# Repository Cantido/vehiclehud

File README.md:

VehicleHUD [![Build Status][ci-img]][ci-link]
=============================================

The purpose of this project is to design and build a projected heads-up
display for a car that is projected on to the windshield. This system will
pull vehicle information from the OBD-II diagnostic jack located in all modern
cars.

Compiling Vehiclehud
--------------------

The main program can be built simply using Make:

```shell
cd src && make
```

Using Vehiclehud
------------------
There is no configuration necessary. Just execute the program that is created
by ```make```. Vehiclehud will attempt to connect to an OBD-II adapter at a
file location defined in the source. If it can connect, it will begin polling
the OBD device for vehicle information and printing the current RPM to
standard output.

OBD-II Adapter Support
----------------------
Currently this software only supports the ELM327 OBD-II adapter. It is a goal
of this project to encapsulate adapter functions so that adding support for
other adapters is possible.

* * * * * * * * * * * * * * * * * * * * * * * * * * * * * * * * * * * * * * * *

Copyright 2013 Robert Richter and Aaron Hall  
Distributed under the terms of the GNU GPL.

[ci-img]: https://travis-ci.org/Cantido/vehiclehud.png?branch=master
[ci-link]: https://travis-ci.org/Cantido/vehiclehud

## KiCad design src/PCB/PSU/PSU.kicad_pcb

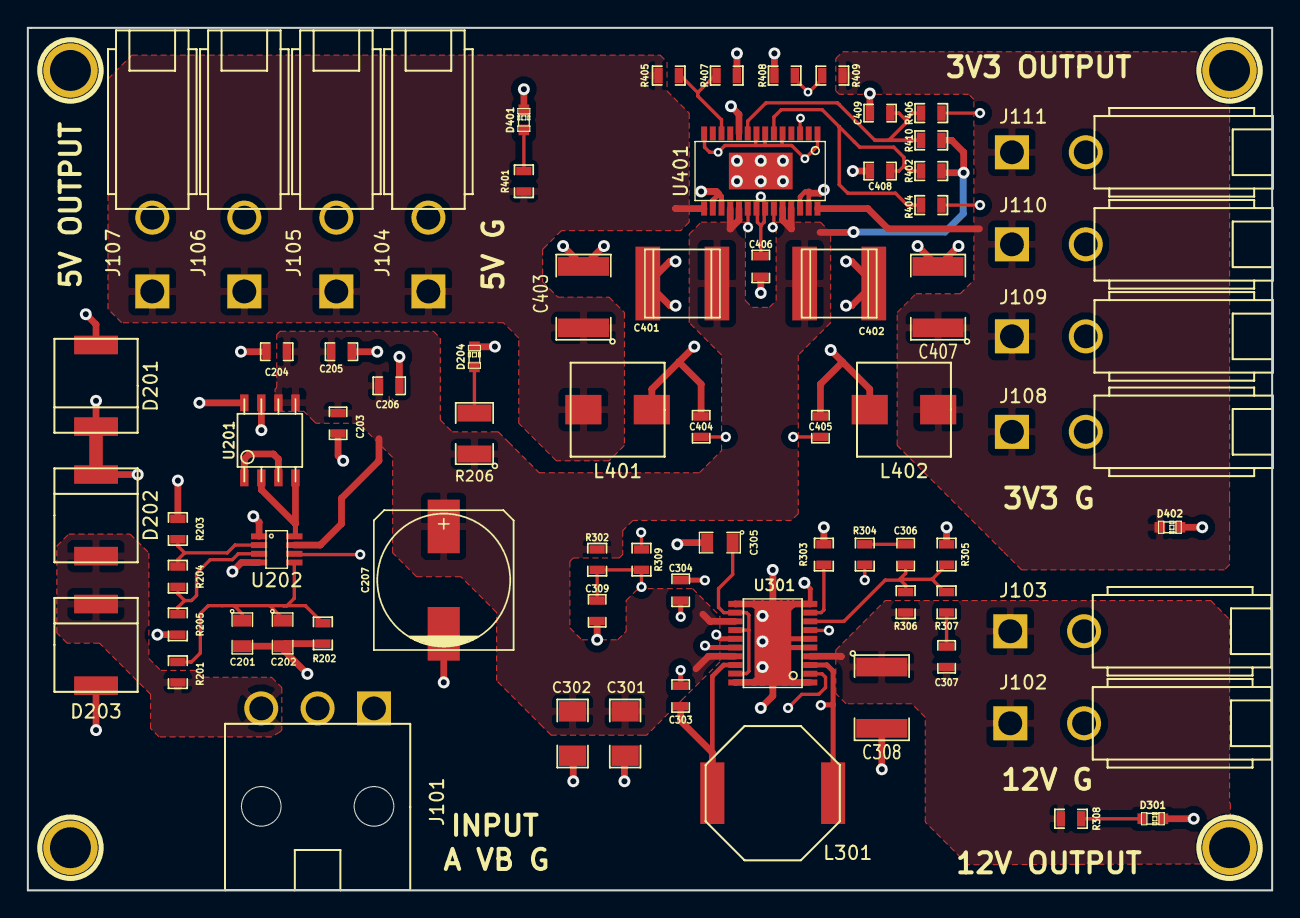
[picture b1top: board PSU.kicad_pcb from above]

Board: 4 copper layers, 92.7 x 64.3 mm, 77 parts (0 on the bottom side), 36 nets.

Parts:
1PIN, 1PIN#2, 1PIN#3, 1PIN#4: P***; 1pin
C201: 0.1uF; SM0805
C202: 0.01uF; SM0805
C203, C204: 0.01u; SM0603_Capa
C205, C206: 0.1u; SM0603_Capa
C207: 100uF; c_elec_10x10
C301, C302: 10uF; SM1206
C303, C304, C309, C404, C405, C408, C409: 0.1uF; SM0603_Capa
C305: 4.7uF; SM0805
C306: 820pF; SM0603_Capa
C307: 33pF; SM0603_Capa
C308, C403, C407: 22uF; SM1812
C401, C402: 47uF; c_2220
C406: 2.2uF; SM0603_Capa
D201, D203: SMCJ40A; DO-214AB(SMC)
D202: SCHOTTKY; DO-214AB(SMC)
D204, D301, D401, D402: BLUE_LED; LED-0603
J101: VIN; mini-fit-jr-3
J102: 12V_1; mini-fit-jr-2
J103: 12V_2; mini-fit-jr-2
J104: 5V_1; mini-fit-jr-2
J105: 5V_2; mini-fit-jr-2
J106: 5V_3; mini-fit-jr-2
J107: 5V_4; mini-fit-jr-2
J108: 3_3V_1; mini-fit-jr-2
J109: 3_3V_2; mini-fit-jr-2
J110: 3_3V_3; mini-fit-jr-2
J111: 3_3V_4; mini-fit-jr-2
L301: 10uH; L10
L401: 1.5uH; L6.9
L402: 1uH; L6.9
R201, R302, R402, R410: 100k; SM0603_Resistor
R202, R307, R407, R408: 10k; SM0603_Resistor
R203: 1.82M; SM0603_Resistor
R204: 243k; SM0603_Resistor
R205: 59k; SM0603_Resistor
R206: 560; SM1210
R303: 35.7k; SM0603_Resistor
R304: 40.2k; SM0603_Resistor
R305: 90.9k; SM0603_Resistor
R306: 1M; SM0603_Resistor
R308: 430; SM0603_Resistor
R309, R404, R406: 0; SM0603_Resistor
R401: 91; SM0603_Resistor
R405: 73.2k; SM0603_Resistor
R409: 45.3k; SM0603_Resistor
U201: SI4946; so-8
U202: LTC4365; tsot-23
U301: LTC3115-1; tssop-20-epad
U401: LTC3633A-1; tssop-28-epad

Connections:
/5V and 3.3V Supply/3_3V: C407.1, D402.1, J108.1, J109.1, J110.1, J111.1, L402.2, R409.2, U401.28
/5V and 3.3V Supply/5V: C403.1, J104.1, J105.1, J106.1, J107.1, L401.1, R401.1, R405.1, U401.15
/12V Supply/12V: C307.1, C308.1, J102.1, J103.1, R306.1, R308.1, U301.4
/12V Supply/RUN: R309.1, R404.1, R406.1, U202.6
/PSU Protection/ACC: D202.1, D203.2, J101.3, R201.1
/PSU Protection/VBATT: D201.2, D202.2, J101.2, R203.1, U201.7, U201.8, U202.1
GND: C201.2, C202.2, C203.2, C204.2, C205.2, C206.2, C207.2, C301.2, C302.2, C305.2, C308.2, C309.2, C401.2, C402.2, C403.2, C406.2, C407.2, C408.2, C409.2, D201.1, D203.1, D204.2, D301.2, D401.2, D402.2, J101.1, J102.2, J103.2, J104.2, J105.2, J106.2, J107.2, J108.2, J109.2, J110.2, J111.2, R202.2, R205.2, R303.2, R305.2, R407.2, R408.2, U202.4, U301.1, U301.5, U301.6, U301.10, U301.11, U301.20, U301.21, U401.10, U401.29
unnamed: C201.1, C202.1, R201.2, R202.1, U202.5
unnamed: D204.1, R206.2
unnamed: R203.2, R204.1, U202.2
unnamed: R204.2, R205.1, U202.3
unnamed: U201.2, U201.4, U202.8
unnamed: U201.1, U201.3
unnamed: C305.1, U301.12, U301.14, U301.19
unnamed: C307.2, R307.1
unnamed: C304.2, U301.15
unnamed: D301.1, R308.2
unnamed: C306.2, R305.1, R306.2, R307.2, U301.8
unnamed: R304.2, U301.7
unnamed: C306.1, R304.1
unnamed: R303.1, U301.9
unnamed: C309.1, R302.2, R309.2, U301.2
unnamed: C303.1, L301.1, U301.18
unnamed: C303.2, U301.16
unnamed: C304.1, L301.2, U301.3
unnamed: C405.1, U401.23
unnamed: C404.1, U401.20
unnamed: C404.2, L401.2, U401.16, U401.17
unnamed: C406.1, U401.1, U401.5, U401.7, U401.8, U401.14, U401.21, U401.22
unnamed: C408.1, R402.2, R404.2, U401.6
unnamed: C409.1, R406.2, R410.2, U401.9
unnamed: D401.1, R401.2
unnamed: C405.2, L402.1, U401.26, U401.27
unnamed: R408.1, R409.1, U401.3
unnamed: R405.2, R407.1, U401.12
VCC: C203.1, C204.1, C205.1, C206.1, C207.1, C301.1, C302.1, C401.1, C402.1, R206.1, R302.1, R402.1, R410.1, U201.5, U201.6, U202.7, U301.13, U301.17, U401.18, U401.19, U401.24, U401.25

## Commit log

2013-05-02 Wrote inital description
2013-05-02 Fixed Markdown formatting
2013-05-02 Minor adjustment to language
2013-05-02 Applied GPL
2013-05-02 Fixed ordered list formatting
2013-05-02 Added a target to clean the folder of .exe files
2013-05-02 Added newline to the end
2013-05-02 Turning on all compiler warnings
2013-05-02 Add serial configuration and initialization code
2013-05-02 Add GNU GPL statement
2013-05-02 Make error messages display target file location
2013-05-02 Extract command variables
2013-05-02 Add stackdump files to clean target
2013-05-02 Improve error handling and feedback
2013-05-02 Add newline to end of file
2013-05-02 Extracted serial connection operations to a function
2013-05-02 Map NL to CR-NL on output
2013-05-02 Disable output translation of newlines. We'll handle this ourselves
2013-05-02 Remove oflag settings, currently uneeded
2013-05-02 Make reads blocking
2013-05-02 Re-enable nonblocking IO for testing purposes
2013-05-02 Add testing feedback to verify communication with ELM chip
2013-05-02 Learn to count
2013-05-02 Fully describe our requirements from the OBD
2013-05-02 Add a missing period
2013-05-02 Replace horizontal rules with proper headers, for GitHub
2013-05-02 Fix printing of carriage return character
2013-05-03 Extract chip read test to a function
2013-05-03 Add forward declaration and variable declaration
2013-05-03 Rename test_reset to obd_init
2013-05-03 Add documentation for functions
2013-05-04 Add function get_data to get data from OBD
2013-05-06 Write carriage return after request to terminate string
2013-05-06 Fix sending of carriage return at end of request string
2013-05-06 Use strtol instead of atoi to correctly parse hex string
2013-05-06 Remove unecessary parameter to get_data
2013-05-06 Remove unused local variables
2013-05-06 Extract line end character to DEFINE directive
2013-05-06 Add some debug printing
2013-05-07 Remove unnecessary variable
2013-05-07 Add forward declaration for get_data
2013-05-07 Create debug loop to print RPM every 2 seconds
    If we make it that far...
2013-05-08 Fix spelling error in previous commit
    Note to self: compile before commit
2013-05-08 Extract OBD PID defintions into its own header
2013-05-08 Add OBD header file to repo
2013-05-08 Extract OBD PID defintions into its own header
    Add OBD header file to repo
2013-05-08 Add z modifier to ssize_t format strings
2013-05-09 Extract get of RPM into a function
2013-05-09 Turn on compiler warnings the correct way
2013-05-09 Extracted OBD data functions to obd.c
2013-05-14 Add .gch files to clean target
2013-05-14 Extracted ELM327-specific functions to elm327.c
    Functions requred by obd.c are now preprocessor defines in obd.c pointing to
    elm327's particular get_elm327_data function
2013-05-14 Add first set of PID definitions
2013-06-17 Create gh-pages branch via GitHub
2013-06-19 Configure for the Raspberry Pi USB port
2013-06-25 Added sample C# project for OBD communication.
2013-08-02 Convert to C++ Project
2013-08-02 Add make target to .travis.yml
2013-08-02 Add Travis-CI build status image
2013-08-02 Convert back to C project
2013-08-02 Convert to C project
2013-08-02 Minor cleanup of compiler and debug warnings
2013-08-13 Remove implementation info from readme, add usage info
2013-08-13 Clarify README language
2013-08-14 Initial add of Image to Byte Array project.
    This C# program will convert a monochrome bitmap to a byte array. The
    byte array is in the correct format for the Noritake 128x64 VFD.
2013-08-14 Initial commit of hardware and firmware.
    Adding initial PCB designs and AVR testing.
2013-08-15 Modify to use GNU Autotools
2013-08-15 Add autogen script to build process
2013-08-15 Make travis build generate Autotools files
2013-08-15 Remove Autoconf version requirement
2013-08-15 Disable Travis's execution of tests, since we have none
2013-08-15 Remove redundancy from Travis build script
2013-08-16 Reorganized
2013-08-16 Modified to use GNU Autotools
2013-08-23 Added main firmware project and the main board PCB project.
2013-08-23 Move all source files into src directory
2013-08-23 Move all datasheets into doc directory
2013-08-23 Remove binary folders
2013-09-03 Updated PCB projects.
2013-09-05 Simplify terminal settings
2013-09-05 Python makes everything better
2013-09-06 Make main print debug info for now
2013-09-06 Update README to reflect migration to Python
2013-09-10 More changes to the main board schematic.
2013-09-17 Refactor device commands and improve IO speed
2013-09-17 Create integrationtests.py containing tests for an installed system
2013-09-17 Move connect functionality out of init and into its own method
2013-09-17 Check your code for syntax before you commit it
2013-09-17 Fix data requests
2013-09-17 Create simple test for data requests
2013-09-18 Move PDFs out of repo and into the Dropbox
2013-09-19 Fix data requests and add several data methods
2013-09-19 Create more tests
2013-09-19 Create prototype display modes
2013-09-19 Add exception handling, and add string members to data functions
2013-09-19 Add more error handling to data requests
2013-09-19 Change MockSerial to MockDevice
    MockDevice inherits from ELM327 and overrides serial and IO methods
    to allow us to test the rest of the class.
2013-09-19 Remove merge stuff
2013-09-19 Add IDLE folder to be ignored
2013-09-19 Properly use string formatting for exception message
2013-09-19 Extract method for splitting a request into mode, pid, and payload
2013-09-19 Allow users to set expected mock response
2013-10-10 Created final report
2013-10-10 Fix typo
2013-10-10 Add LaTeX-specific files to .gitignore
2013-10-10 Refactor data request function
    There's a lot of nasty static methods in here now, though. :c
2013-10-10 Put executive summary in present and past tense
2013-10-10 Update project team section for present tense
2013-10-10 Update Aaron's email address
2013-10-10 Move each section to its own file
2013-10-10 Create files for each section
2013-10-10 Create introduction
2013-10-14 Add references
2013-10-14 Move image to display after section starts
2013-10-14 Draft project objectives
2013-10-14 Add more LaTeX types to gitignore
    From https://github.com/github/gitignore/blob/master/LaTeX.gitignore
2013-10-14 Add more Python types to gitignore
    From https://github.com/github/gitignore/blob/master/Python.gitignore
2013-10-19 added OBD code implemented in C
2013-10-22 Fix compile errors and add debug print statements
2013-10-22 Refactor: extract baud and read method
    Also modified formatting of entire file since I tore it up while working
2013-10-22 Refactor: extract initialization segment
2013-10-22 Remove unused buffer
2013-10-22 Remove an unnecessary sleep while reading
2013-10-22 Extract method to get RPM
2013-10-22 Remove unused variables
2013-10-22 Refactor: extract more methods
2013-10-22 Refactor: make formatting consistent
    Used GNU Indent with the -linux option
2013-10-23 Fix "ON" detection
2013-10-23 Add Makefile for C code
2013-10-23 Set Travis to build C code
2013-10-24 updated obd code
2013-10-24 Fix compile errors
2013-10-24 Change formatting
2013-10-24 Add formatting target to makefile
2013-10-24 Extracted logic for getting bytes from the ELM
2013-10-24 Bug fix
2013-10-24 Format
2013-10-24 Enable all compiler warnings
2013-10-31 Transfer code base to C
2013-10-31 Append newline to end of README
2013-10-31 Add description of RasPi & software design
2013-10-31 Create a Makefile
2013-10-31 Change to report documentclass with chapters
    Also put newlines at the end of a few files
2013-10-31 Put newline at end of file
    Also known as "Make GitHub stop complaining"
2013-10-31 Fix format
2013-10-31 Rename obdtest to vhudpi and tidy up makefile
2013-11-01 Fix Travis's errors
2013-11-01 Append newline to end of file
2013-11-01 Add comments with section specifications
2013-11-03 Bugfixes
2013-11-03 Make sure your code compiles before you push it
2013-11-03 Fixing issues with character count
2013-11-03 Fix null pointer issue
2013-11-03 I am bad at using malloc
2013-11-03 Added delays in main loop. Added alternate numchars count.
2013-11-04 Add several more OBD data functions
2013-11-04 Remove unused variable
2013-11-04 Added modified vhudpi file
2013-11-04 Updated AVR Test
    Added struct for avr data
2013-11-04 Fix compiler warning
2013-11-04 Remove explicitly setting compiler
2013-11-04 Added descriptions of main board and power supply to report
2013-11-04 LaTeX-ify text
2013-11-04 Remove duplicate line
2013-11-05 Updated vhudpi to wait for '>'
2013-11-06 Remove need for obd_read to count characters
    It reads until '>' so the parameter is useless
2013-11-06 Fix compiler errors
2013-11-06 Make CFLAGS append instead of overwrite
2013-11-06 Add several document options
2013-11-07 Minor edits from proofreading
2013-11-07 Add a lot of datasheet references
2013-11-07 Fix broken citation
2013-11-12 Add Raspberry Pi specifications
2013-11-12 Add a To-do list package and insert todo's
2013-11-12 Bugfixes and refactoring
2013-11-12 Formatting
2013-11-13 TODO necessary figures
2013-11-13 Outlined budget section
2013-11-13 Add more budget data
2013-11-14 Bit o' organizing
2013-11-19 Add ability to install the Pi daemon to start on boot
2013-11-19 Fix some bugs and hope it works
2013-11-20 Make vhudpi run inthe background on startup
2013-11-27 Extract AVR code
2013-11-28 Extract OBD code
2013-12-07 Add time-logging statements in main loop
2013-12-07 Add object files to clean target
2013-12-09 Added optics section
2013-12-09 Timeline and Deliverables section written
2013-12-09 Add some words to Experimental Results
    Pending an actual gathering of data
2013-12-09 Add data to Project Specifications
2013-12-09 Add images to Detailed Design, discuss C code
2013-12-09 Fix images
2013-12-09 Correct information
2013-12-09 Updated PSU section
2013-12-09 Proofreading edits, add images
